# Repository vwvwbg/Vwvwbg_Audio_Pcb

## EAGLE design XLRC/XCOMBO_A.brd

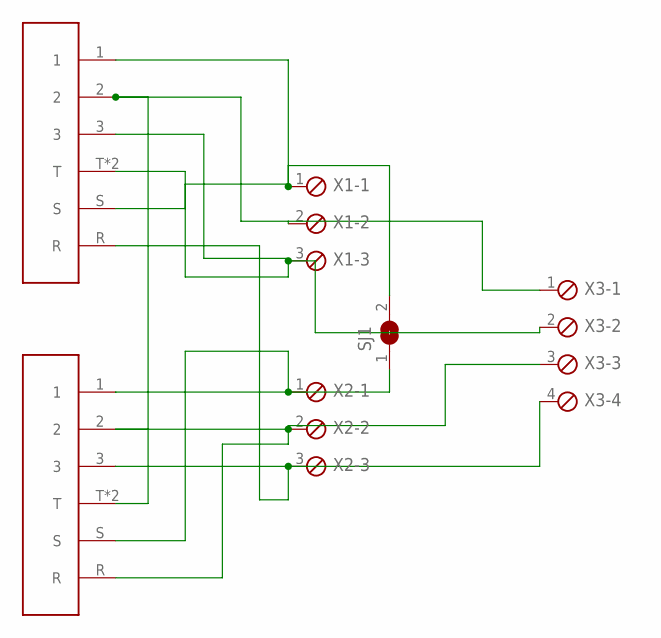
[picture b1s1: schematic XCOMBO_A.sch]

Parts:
SJ1: SJ
U$1, U$2: XLRCOMBOTYPEA; NCJ6FA-V-0
X1, X2: MPT3; 3POL254
X3: MPT4; 4POL254

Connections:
L+: U$1.T, U$1.T2 (T), U$2.2, X1.2, X3.1
L-: U$2.3, U$2.T, U$2.T2 (T), X1.3, X3.2
LG: SJ1.2, U$2.1, U$2.S, X1.1
R+: U$1.2, U$1.R, X2.2, X3.3
R-: U$1.3, U$2.R, X2.3, X3.4
RG: SJ1.1, U$1.1, U$1.S, X2.1

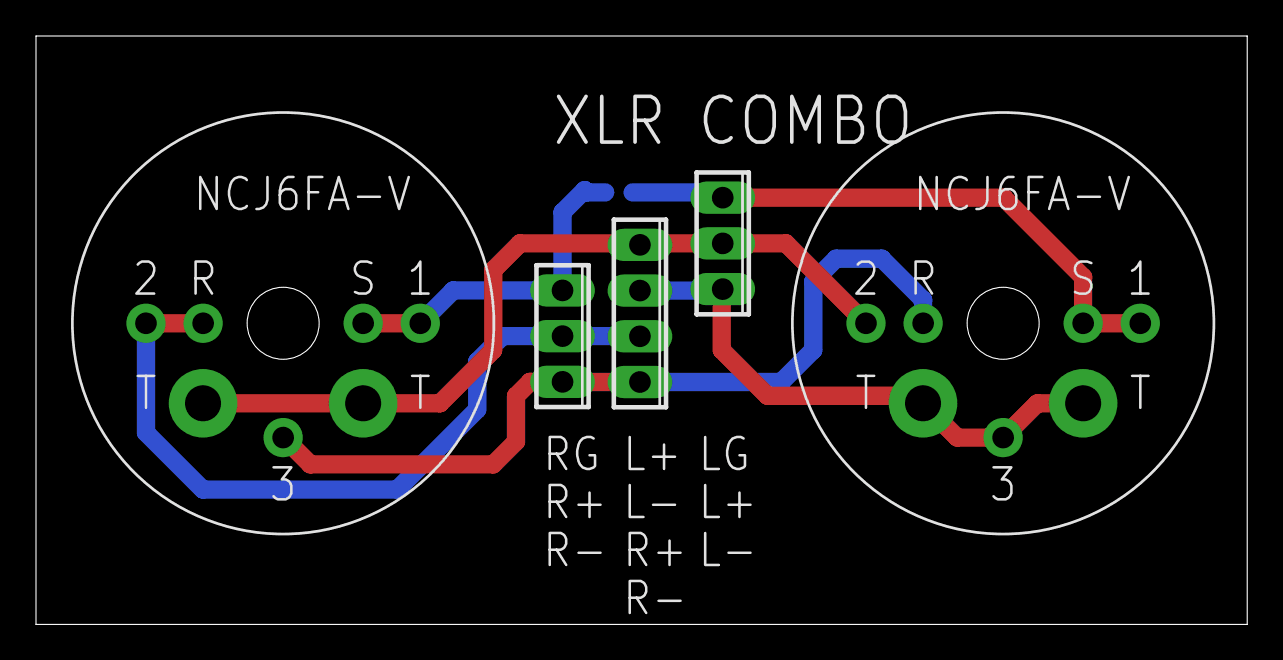
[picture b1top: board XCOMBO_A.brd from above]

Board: 2 copper layers, 67.3 x 32.7 mm, 6 parts (1 on the bottom side), 6 nets.

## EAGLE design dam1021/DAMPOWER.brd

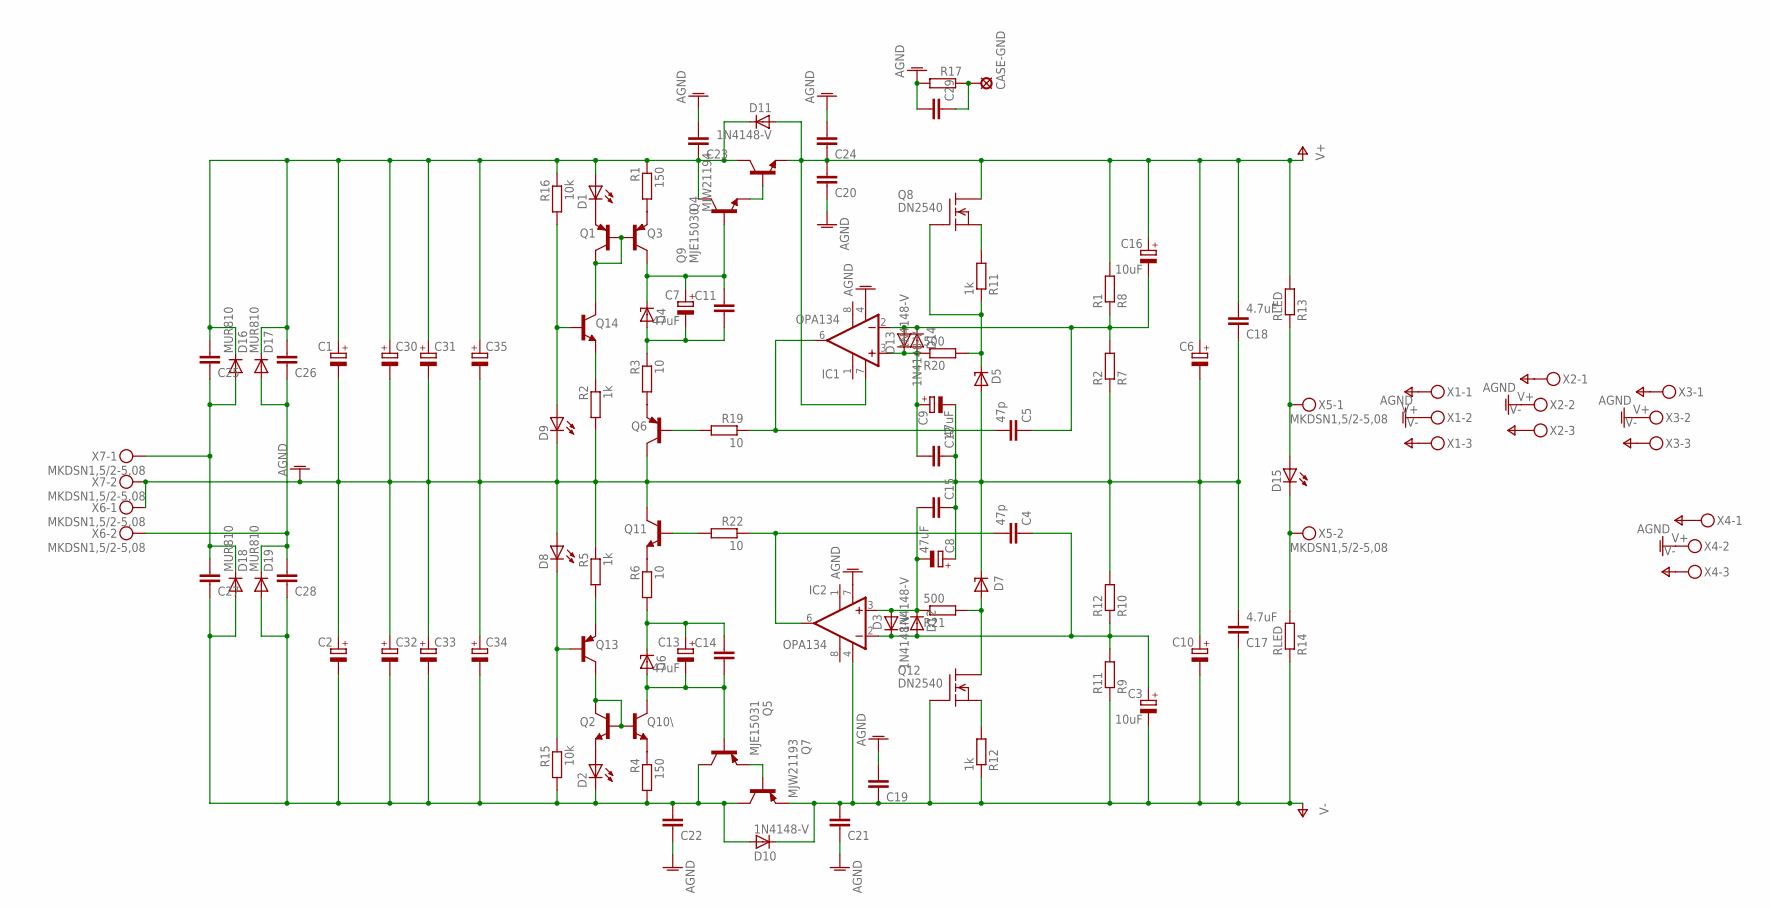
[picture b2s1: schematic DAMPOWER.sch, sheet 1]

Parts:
C1, C2: CPOL-EUE10-35; EB35D
C3, C16: 10uF; E5-8,5
C4, C5: 47p; C025_050-025X075
C6, C10, C30, C31, C32, C33, C34, C35: CPOL-EUE7.5-18; E7,5-18
C7, C8, C9, C13: 47uF; E5-8,5
C11, C12, C14, C15, C19, C20, C21, C24, C25, C26, C27, C28: C-EU050-035X075; C050-035X075
C17, C18: 4.7uF; C050-075X075
C22, C23: C-EU050-075X075; C050-075X075
C29: C-EU102_152-062X184; C102_152-062X184
CASE-GND: SE14
D1, D2, D8, D9, D15: LED5MM
D3, D10, D11, D12, D13, D14: 1N4148-V; 1N4148
D4, D6: 1N4728; DO41Z10
D5, D7: LT1021; DIL08
D16, D17, D18, D19: MUR810; TO220ACS
IC1, IC2: OPA134; DIL08
Q1, Q3, Q6, Q13: MPSA92-PNP-TO92-EBC; TO92-EBC
Q2, Q10\, Q11, Q14: MPSA42-NPN-TO92-EBC; TO92-EBC
Q4: MJW21194; TO-264
Q5: MJE15031; TO220KG
Q7: MJW21193; TO-264
Q8, Q12: DN2540; TO92-
Q9: MJE15030; TO220KG
R1, R4: 150; 0309/12
R2, R5, R11, R12: 1k; 0309/12
R3, R6, R19, R22: 10; 0309/12
R7: R2; 0309/12
R8: R1; 0309/12
R9: R11; 0309/12
R10: R12; 0309/12
R13, R14: RLED; 0309/12
R15, R16: 10k; 0309/12
R17: R-EU_0617/22; 0617/22
R20, R21: 500; 0309/12
X1, X2, X3, X4: MKDSN1,5/3-5,08
X5, X6, X7: MKDSN1,5/2-5,08

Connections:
AGND: C1.-, C2.+, C6.-, C8.+, C9.-, C10.+, C12.1, C15.1, C17.2, C18.1, C19.2, C20.1, C21.1, C22.1, C23.2, C24.2, C29.2, C29.3 (2), C30.-, C31.-, C32.+, C33.+, C34.+, C35.-, D5.4 (GND), D7.6 (OUT), D8.A, D9.K (C), IC1.4 (V-), IC2.7 (V+), Q6.C, Q11.C, R2.2, R5.1, R7.1, R10.2, R17.2, X1.2, X2.2, X3.2, X4.2, X6.1, X7.2
unnamed: Q1.B, Q1.C, Q3.B, Q14.C
unnamed: D1.K (C), Q1.E
unnamed: Q3.E, R1.2
unnamed: C1.+, C23.1, C25.2, C26.2, C30.+, C31.+, C35.+, D1.A, D11.C, D16.C, D17.C, Q4.C, Q9.2 (C), R1.1, R16.1
unnamed: C7.+, C11.1, D4.C, Q3.C, Q9.1 (B)
unnamed: C7.-, C11.2, D4.A, R3.1
unnamed: Q6.E, R3.2
unnamed: Q14.E, R2.1
unnamed: D9.A, Q14.B, R16.2
unnamed: C8.-, C15.2, D3.A, D12.C, IC2.3 (+IN), R21.1
unnamed: Q13.E, R5.2
unnamed: D8.K (C), Q13.B, R15.1
unnamed: Q11.E, R6.1
unnamed: C13.+, C14.1, D6.C, R6.2
unnamed: C13.-, C14.2, D6.A, Q5.1 (B), Q10\.C
unnamed: Q2.B, Q2.C, Q10\.B, Q13.C
unnamed: Q5.3 (E), Q7.B
unnamed: Q10\.E, R4.1
unnamed: D2.A, Q2.E
unnamed: Q4.B, Q9.3 (E)
unnamed: C2.-, C22.2, C27.1, C28.1, C32.-, C33.-, C34.-, D2.K (C), D10.A, D18.A, D19.A, Q5.2 (C), Q7.C, R4.2, R15.2
unnamed: C25.1, C27.2, D16.A, D18.C, X7.1
unnamed: C5.2, C5.3 (2), IC1.6 (OUT), R19.1
unnamed: C4.2, C4.3 (2), IC2.6 (OUT), R22.1
unnamed: Q11.B, R22.2
unnamed: Q6.B, R19.2
unnamed: C5.1, C16.-, D13.A, D14.C, IC1.2 (-IN), R7.2, R8.1
unnamed: Q12.3 (S), R12.2
unnamed: D5.6 (OUT), Q8.2 (G), R11.1, R20.2
unnamed: C9.+, C12.2, D13.C, D14.A, IC1.3 (+IN), R20.1
unnamed: D15.K (C), R14.2, X5.2
unnamed: D7.4 (GND), Q12.1 (D), R21.2
unnamed: C3.+, C4.1, D3.C, D12.A, IC2.2 (-IN), R9.2, R10.1
unnamed: Q8.3 (S), R11.2
unnamed: D15.A, R13.1, X5.1
unnamed: C26.1, C28.2, D17.A, D19.C, X6.2
unnamed: C29.1, CASE-GND.MP, R17.1
V+: C6.+, C16.+, C18.2, C20.2, C24.1, D11.A, IC1.7 (V+), Q4.E, Q8.1 (D), R8.2, R13.2, X1.1, X2.1, X3.1, X4.1
V-: C3.-, C10.-, C17.1, C19.1, C21.2, D10.C, IC2.4 (V-), Q7.E, Q12.2 (G), R9.1, R12.1, R14.1, X1.3, X2.3, X3.3, X4.3

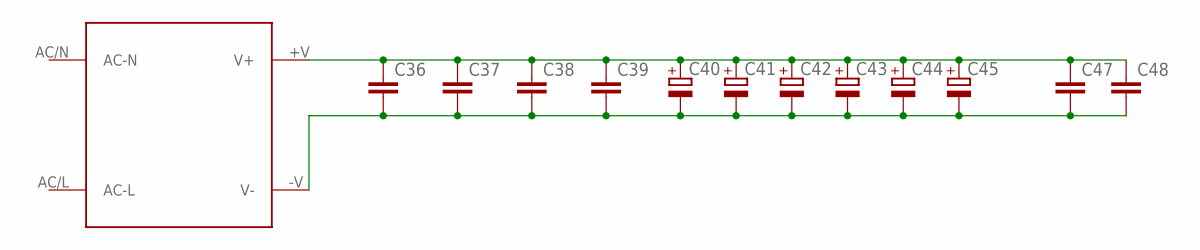
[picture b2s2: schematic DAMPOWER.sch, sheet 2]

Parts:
C36, C37, C38, C39, C47, C48: C-EU050-030X075; C050-030X075
C40, C41, C42, C43, C44, C45: CPOL-EUE3.5-8; E3,5-8
U$1: IRM-15-5; IRM-15

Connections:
unnamed: C36.1, C37.1, C38.1, C39.1, C40.+, C41.+, C42.+, C43.+, C44.+, C45.+, C47.1, C48.1, U$1.+V (V+)
unnamed: C36.2, C37.2, C38.2, C39.2, C40.-, C41.-, C42.-, C43.-, C44.-, C45.-, C47.2, C48.2, U$1.-V (V-)

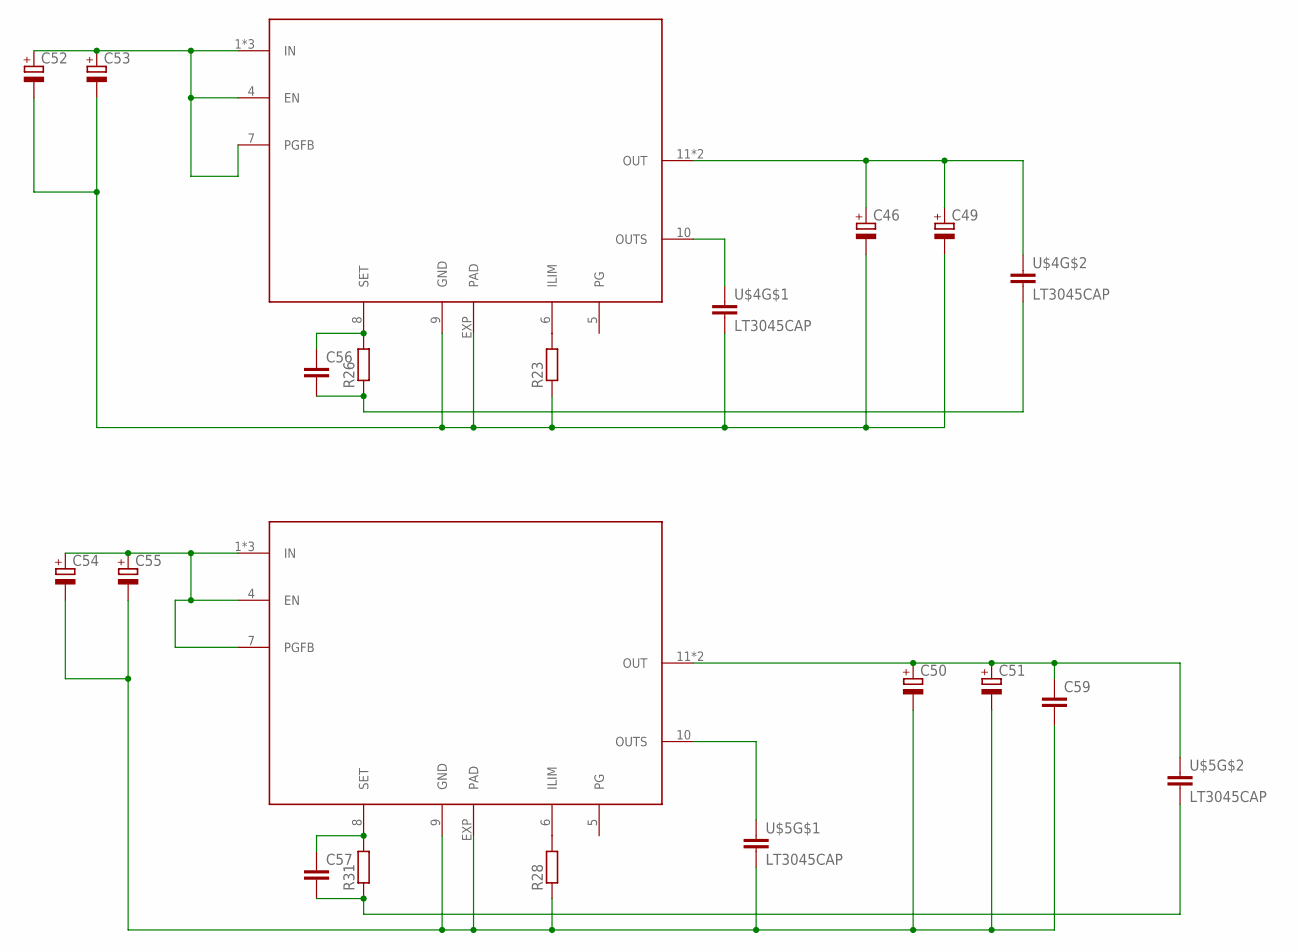
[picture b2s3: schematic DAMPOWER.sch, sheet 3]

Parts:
C46, C49, C50, C51: CPOL-EUE3.5-8; E3,5-8
C52, C53, C54, C55: CPOL-EUE5-10.5; E5-10,5
C56, C57, C59: C-EUC1210; C1210
R23, R26, R28, R31: R-EU_MELF0204R; MINI_MELF-0204R
U$2, U$3: LT3045; MSOP12
U$4, U$5: LT3045CAP

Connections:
unnamed: C52.+, C53.+, U$2.1 (IN), U$2.2 (IN), U$2.3 (IN), U$2.4 (EN), U$2.7 (PGFB)
unnamed: R23.2, U$2.6 (ILIM)
unnamed: C56.1, R26.2, U$2.8 (SET)
unnamed: R28.2, U$3.6 (ILIM)
unnamed: C57.1, R31.2, U$3.8 (SET)
unnamed: U$2.10 (OUTS), U$4.3 (1)
unnamed: C46.-, C49.-, C52.-, C53.-, R23.1, U$2.9 (GND), U$2.EXP (PAD), U$4.5 (2)
unnamed: C46.+, C49.+, U$2.11 (OUT), U$2.12 (OUT), U$4.4 (1)
unnamed: U$3.10 (OUTS), U$5.3 (1)
unnamed: C50.-, C51.-, C54.-, C55.-, C59.2, R28.1, U$3.9 (GND), U$3.EXP (PAD), U$5.5 (2)
unnamed: C56.2, R26.1, U$4.6 (2)
unnamed: C54.+, C55.+, U$3.1 (IN), U$3.2 (IN), U$3.3 (IN), U$3.4 (EN), U$3.7 (PGFB)
unnamed: C57.2, R31.1, U$5.6 (2)
unnamed: C50.+, C51.+, C59.1, U$3.11 (OUT), U$3.12 (OUT), U$5.4 (1)

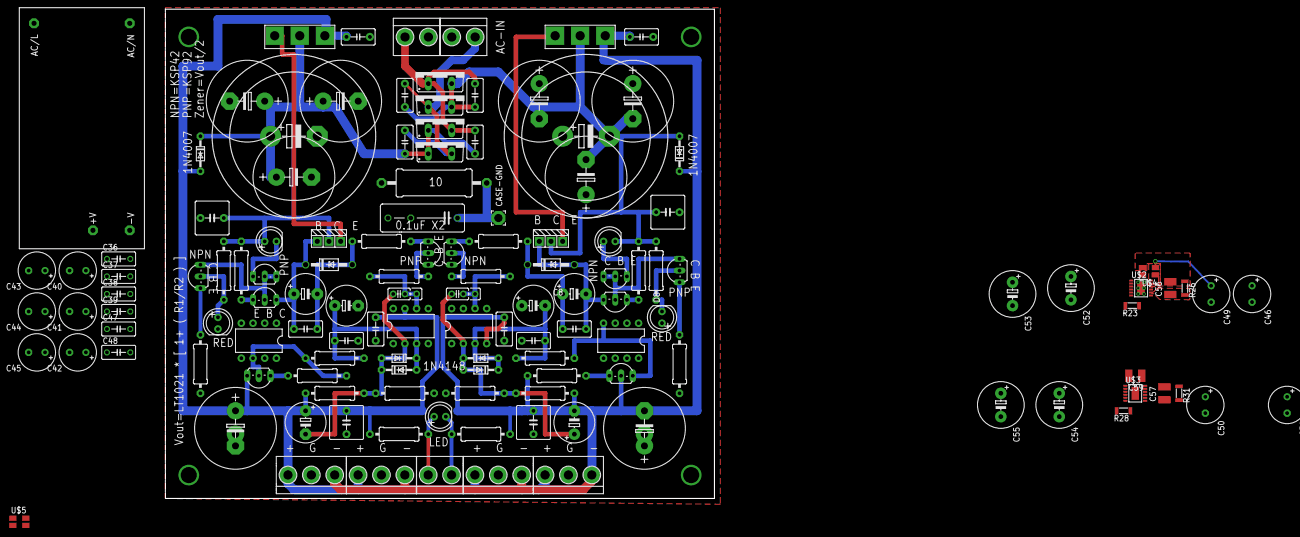
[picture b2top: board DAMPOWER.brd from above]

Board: 2 copper layers, 119.4 x 106.3 mm, 131 parts (0 on the bottom side), 56 nets.

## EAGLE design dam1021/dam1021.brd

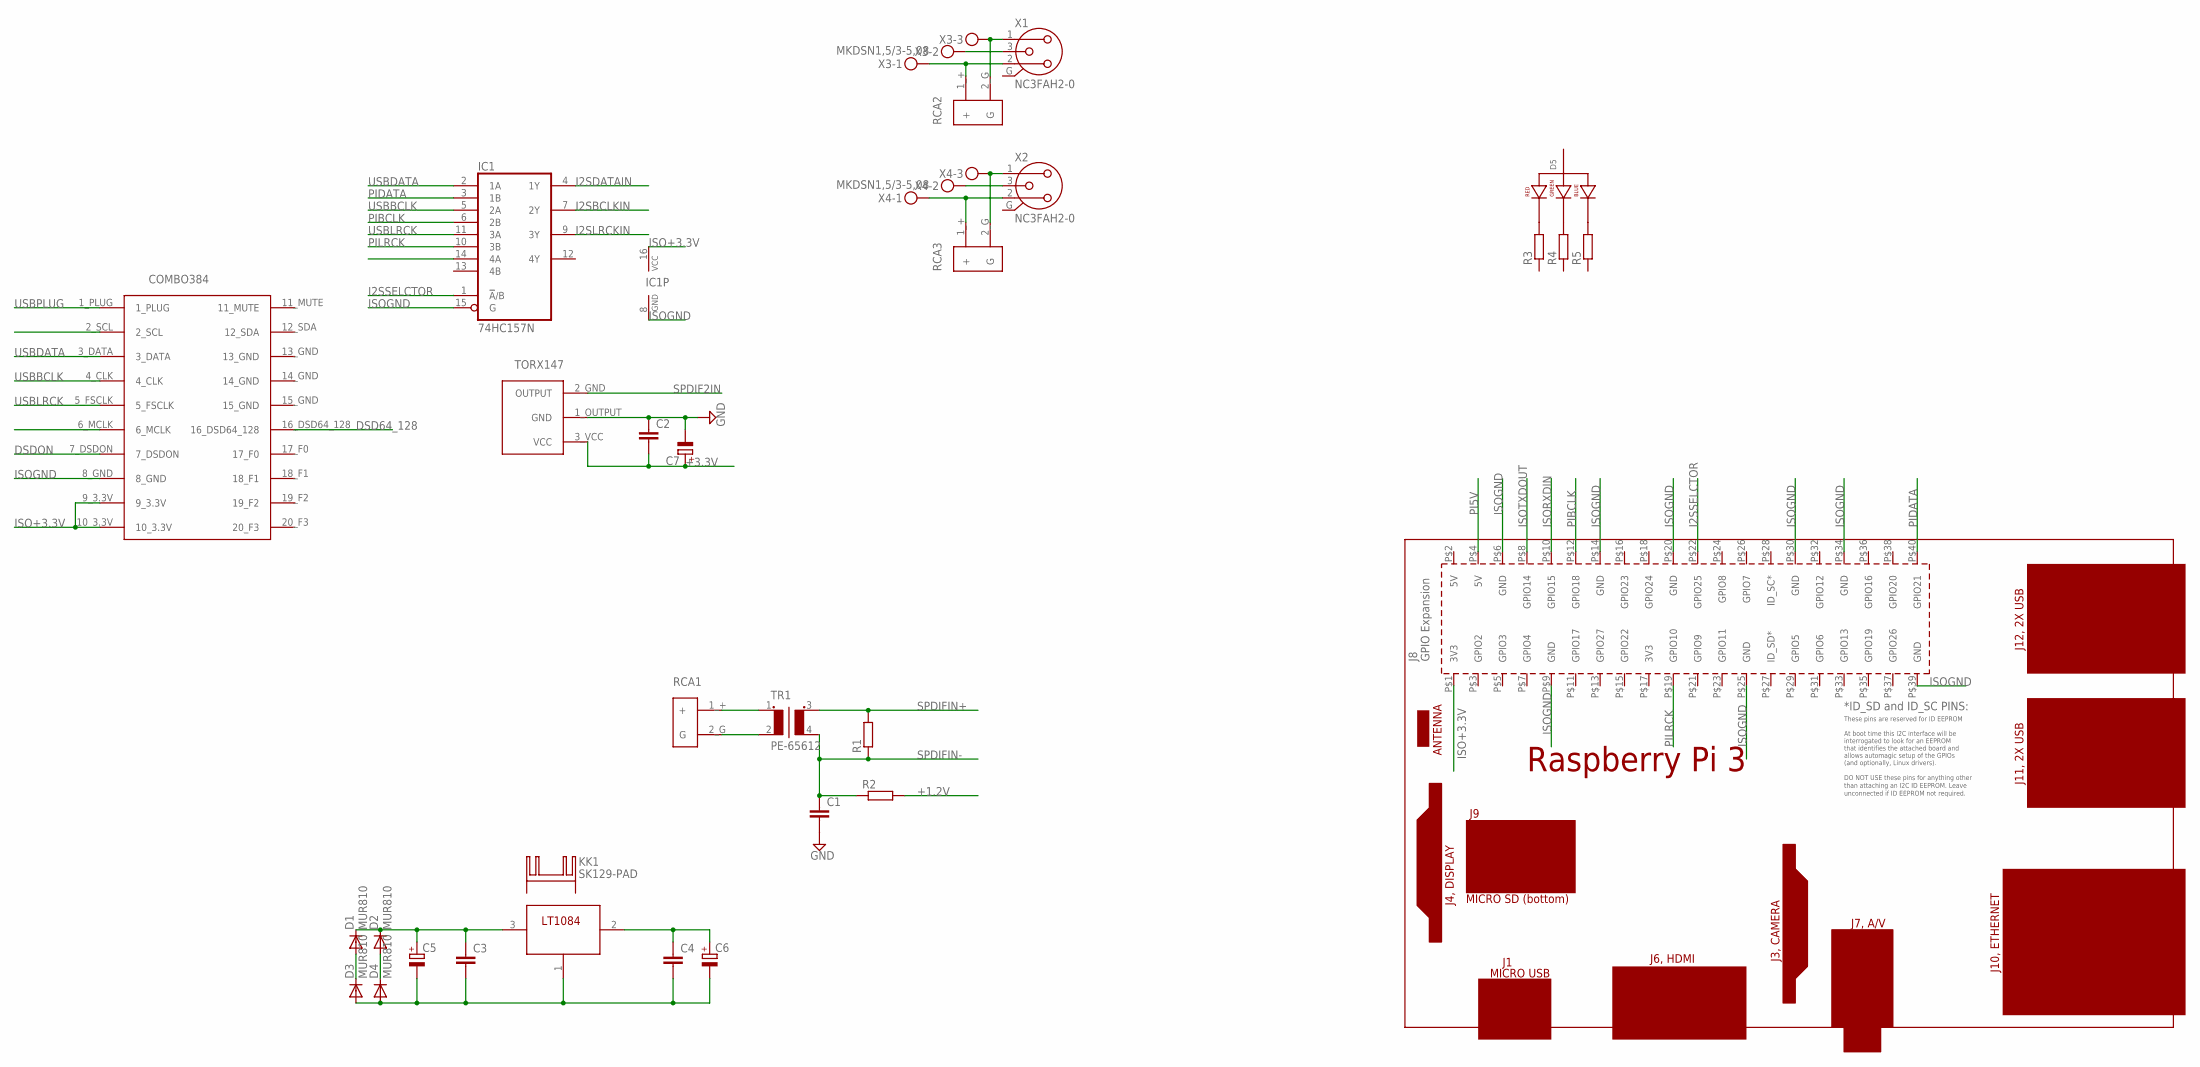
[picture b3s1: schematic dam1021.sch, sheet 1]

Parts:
C1, C2, C3, C4: C-EU050-035X075; C050-035X075
C5: CPOL-EUE7.5-16; E7,5-16
C6: CPOL-EUE5-10.5; E5-10,5
C7: CPOL-EUE2.5-7; E2,5-7
D1, D2, D3, D4: MUR810; TO220ACS
D5: LED-RGB-CA-THRUCLEAR; LED-RGB-THRU
IC1: 74HC157N; DIL16
KK1: SK129-PAD; SK129
PCB1: RPI3
R1, R2, R3, R4, R5: R-EU_0207/10; 0207/10
RCA1, RCA2, RCA3: RCA
TR1: PE-65612
U$2: TORX147
U$3: COMBO384
U$5: LT1084; TO-220
X1, X2: NC3FAH2-0
X3, X4: MKDSN1,5/3-5,08

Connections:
+1.2V: R2.2; also elsewhere on the board
+3.3V: C2.2, C7.+, U$2.3_VCC (VCC); also elsewhere on the board
AGND: RCA2.2_G (G), RCA3.2_G (G), X1.1, X2.1, X3.3, X4.3; also elsewhere on the board
DSD64_128: U$3.16_DSD64_128
DSDON: U$3.7_DSDON
GND: C1.2, C2.1, C7.-, U$2.1_OUTPUT (GND); also elsewhere on the board
I2SBCLKIN: IC1.7 (2Y); also elsewhere on the board
I2SDATAIN: IC1.4 (1Y); also elsewhere on the board
I2SLRCKIN: IC1.9 (3Y); also elsewhere on the board
I2SSELCTOR: IC1.1 (!A!/B), PCB1.P$22 (GPIO25)
ISO+3.3V: IC1.16 (VCC), PCB1.P$1 (3V3), U$3.9_3.3V, U$3.10_3.3V; also elsewhere on the board
ISOGND: C3.2, C4.2, C5.-, C6.-, D3.A, D4.A, IC1.8 (GND), IC1.15 (G), PCB1.P$6 (GND), PCB1.P$9 (GND), PCB1.P$14 (GND), PCB1.P$20 (GND), PCB1.P$25 (GND), PCB1.P$30 (GND), PCB1.P$34 (GND), PCB1.P$39 (GND), U$3.8_GND, U$5.1; also elsewhere on the board
ISORXDIN: PCB1.P$10 (GPIO15); also elsewhere on the board
ISOTXDOUT: PCB1.P$8 (GPIO14); also elsewhere on the board
unnamed: RCA1.1_+ (+), TR1.1
unnamed: RCA1.2_G (G), TR1.2 (3)
unnamed: D5.1 (RED_CATHODE), R3.2
unnamed: D5.3 (GREEN_CATHODE), R4.2
unnamed: C3.1, C5.+, D1.C, D2.C, U$5.3
unnamed: D1.A, D3.C
unnamed: D2.A, D4.C
unnamed: D5.4 (BLUE_CATHODE), R5.2
unnamed: X1.3, X3.2
unnamed: RCA2.1_+ (+), X1.2, X3.1
unnamed: X2.3, X4.2
unnamed: RCA3.1_+ (+), X2.2, X4.1
PI5V: C4.1, C6.+, PCB1.P$4 (5V), U$5.2
PIBCLK: IC1.6 (2B), PCB1.P$12 (GPIO18)
PIDATA: IC1.3 (1B), PCB1.P$40 (GPIO21)
PILRCK: IC1.10 (3B), PCB1.P$19 (GPIO10)
SPDIF2IN: U$2.2_GND (OUTPUT); also elsewhere on the board
SPDIFIN+: R1.2, TR1.3 (6); also elsewhere on the board
SPDIFIN-: C1.1, R1.1, R2.1, TR1.4; also elsewhere on the board
USBBCLK: IC1.5 (2A), U$3.4_CLK
USBDATA: IC1.2 (1A), U$3.3_DATA
USBLRCK: IC1.11 (3A), U$3.5_FSCLK
USBPLUG: U$3.1_PLUG

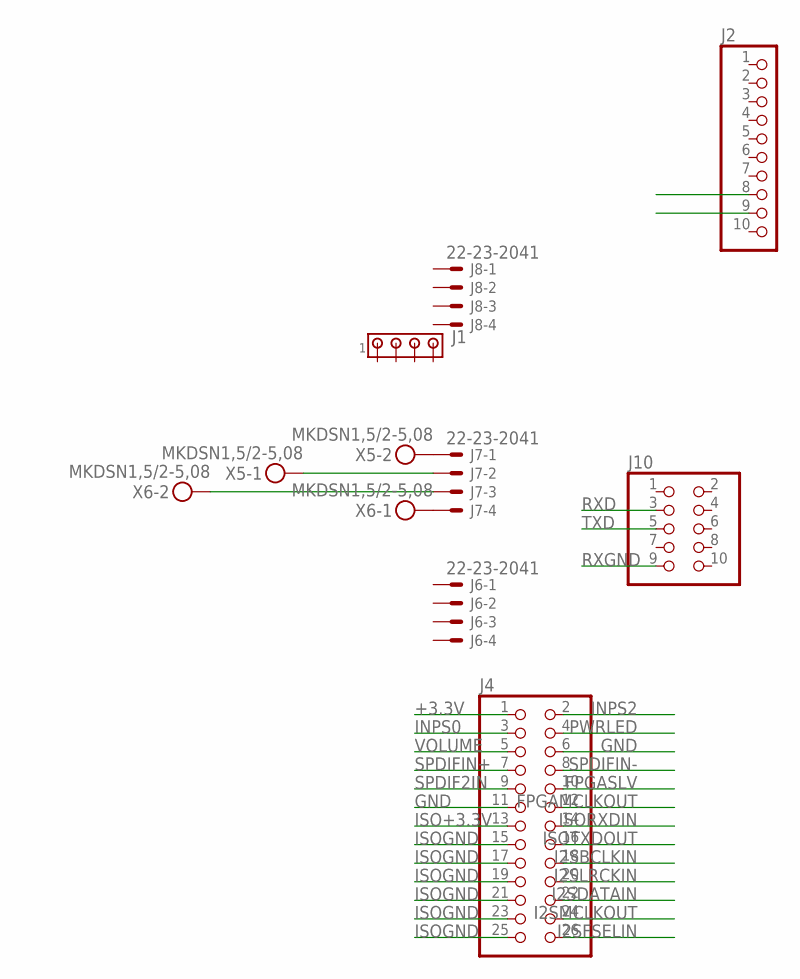
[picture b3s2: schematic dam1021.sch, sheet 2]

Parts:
J1: MTA04-156; 1X4MTA
J2: PINHD-1X10; 1X10
J4: PINHD-2X13; 2X13
J6, J7, J8: 22-23-2041
J10: PINHD-2X5; 2X05
X5, X6: MKDSN1,5/2-5,08

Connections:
+1.2V: J2.9; also elsewhere on the board
+3.3V: J2.8, J4.1; also elsewhere on the board
AGND: J7.2, J7.3, X5.1, X6.2; also elsewhere on the board
FPGAMCLKOUT: J4.12
FPGASLV: J4.10
GND: J4.6, J4.11; also elsewhere on the board
I2SBCLKIN: J4.18; also elsewhere on the board
I2SDATAIN: J4.22; also elsewhere on the board
I2SFSELIN: J4.26
I2SLRCKIN: J4.20; also elsewhere on the board
I2SMCLKOUT: J4.24
INPS0: J4.3
INPS2: J4.2
ISO+3.3V: J4.13; also elsewhere on the board
ISOGND: J4.15, J4.17, J4.19, J4.21, J4.23, J4.25; also elsewhere on the board
ISORXDIN: J4.14; also elsewhere on the board
ISOTXDOUT: J4.16; also elsewhere on the board
unnamed: J7.1, X5.2
unnamed: J7.4, X6.1
PWRLED: J4.4
RXD: J10.3
RXGND: J10.9
SPDIF2IN: J4.9; also elsewhere on the board
SPDIFIN+: J4.7; also elsewhere on the board
SPDIFIN-: J4.8; also elsewhere on the board
TXD: J10.5
VOLUME: J4.5

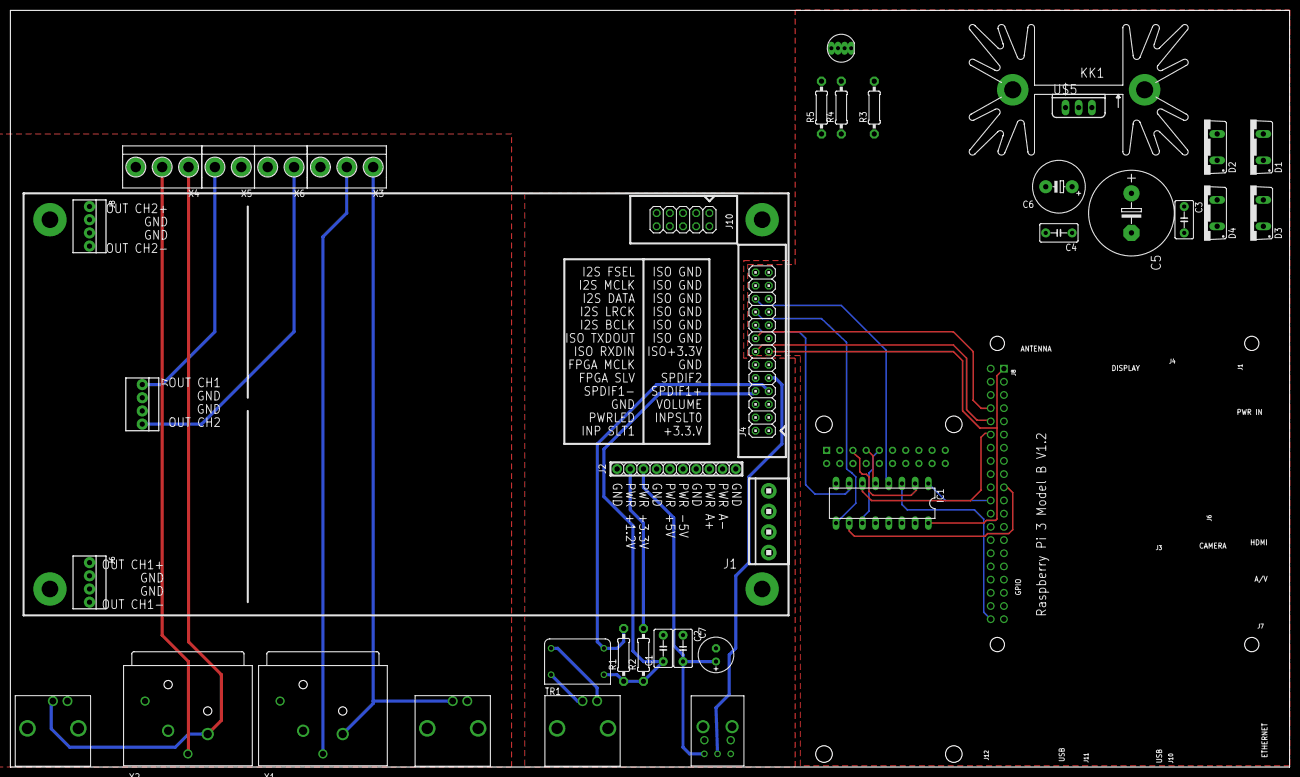
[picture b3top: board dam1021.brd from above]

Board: 2 copper layers, 246.4 x 145.7 mm, 40 parts (0 on the bottom side), 36 nets.

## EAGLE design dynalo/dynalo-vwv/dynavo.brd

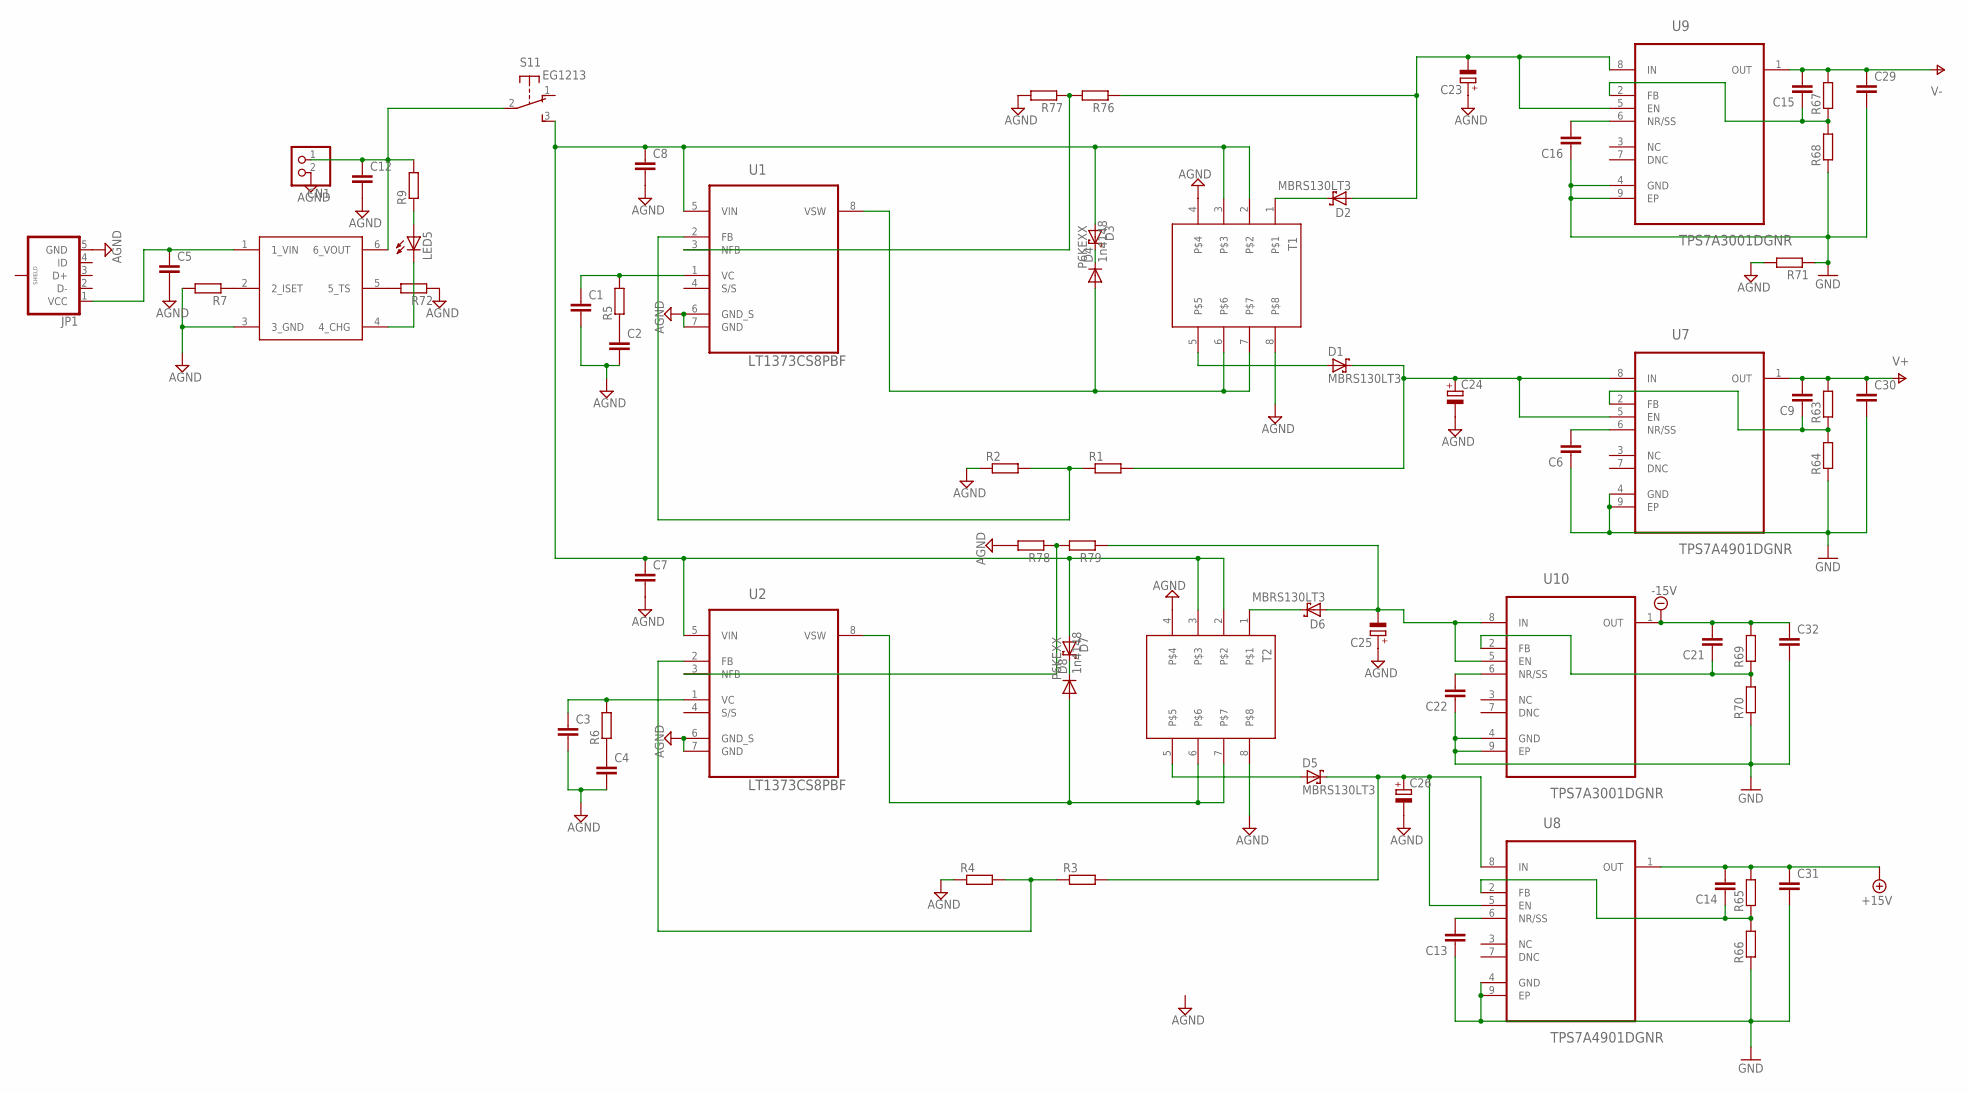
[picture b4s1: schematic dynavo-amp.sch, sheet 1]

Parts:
C1, C2, C3, C4, C5, C7, C8, C12: C-EUC1210; C1210
C6, C9, C13, C14, C15, C16, C21, C22, C29, C30, C31, C32: C-EUC1206; C1206
C23, C24, C25, C26: CPOL-EUD/7343-31W; D/7343-31W
CN1: JST_2PIN-THM; JST-PH-2-THM
D1, D2, D5, D6: MBRS130LT3; SMB
D3, D7: P6KEXX; SMBJ
D4, D8: 1n4148; SOD80C
JP1: USB_MICROB_PLUG-SMT; MICRO-B-SMT
LED5: LED3MM
R1, R2, R3, R4, R5, R6, R7, R9, R63, R64, R65, R66, R67, R68, R69, R70, R71, R72, R76, R77, R78, R79: R-EU_MELF0204W; MINI_MELF-0204W
S1: EG1213
T1, T2: LPE4841
U1, U2: LT1373CS8PBF; SOIC127P600X175-8N
U3: BQ21040; SOT-23-6
U7, U8: TPS7A4901DGNR; SOP65P490X110-9N
U9, U10: TPS7A3001DGNR; SOP65P490X110-9N

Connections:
+15V: C14.2, C31.1, R65.2, U8.1 (OUT); also elsewhere on the board
-15V: C21.2, C32.1, R69.2, U10.1 (OUT); also elsewhere on the board
AGND: C1.2, C2.2, C3.2, C4.2, C5.2, C7.2, C8.2, C12.2, C23.+, C24.-, C25.+, C26.-, CN1.2 (1), JP1.5 (GND), R2.1, R4.1, R7.2, R71.2, R72.1, R77.2, R78.2, T1.4, T1.8, T2.4, T2.8, U1.6 (GND_S), U1.7 (GND), U2.6 (GND_S), U2.7 (GND), U3.3 (3_GND)
GND: C6.1, C13.1, C16.1, C22.1, C29.2, C30.2, C31.2, C32.2, R64.1, R66.1, R68.1, R70.1, R71.1, U7.4 (GND), U7.9 (EP), U8.4 (GND), U8.9 (EP), U9.4 (GND), U9.9 (EP), U10.4 (GND), U10.9 (EP); also elsewhere on the board
unnamed: D3.C, D4.C
unnamed: C7.1, C8.1, D3.A, D7.A, S1.3 (S), T1.2, T1.3, T2.2, T2.3, U1.5 (VIN), U2.5 (VIN)
unnamed: D4.A, T1.6, T1.7, U1.8 (VSW)
unnamed: D2.C, T1.1
unnamed: D1.A, T1.5
unnamed: R1.1, R2.2, U1.2 (FB)
unnamed: R7.1, U3.2 (2_ISET)
unnamed: D7.C, D8.C
unnamed: D8.A, T2.6, T2.7, U2.8 (VSW)
unnamed: D6.C, T2.1
unnamed: D5.A, T2.5
unnamed: R3.1, R4.2, U2.2 (FB)
unnamed: C1.1, R5.2, U1.1 (VC)
unnamed: C3.1, R6.2, U2.1 (VC)
unnamed: C2.1, R5.1
unnamed: C4.1, R6.1
unnamed: LED5.A, R9.1
unnamed: C5.1, JP1.1 (VCC), U3.1 (1_VIN)
unnamed: C24.+, D1.C, R1.2, U7.5 (EN), U7.8 (IN)
unnamed: C23.-, D2.A, R76.1, U9.5 (EN), U9.8 (IN)
unnamed: C12.1, CN1.1 (2), R9.2, S1.2, U3.6 (6_VOUT)
unnamed: LED5.K (C), U3.4 (4_CHG)
unnamed: C26.+, D5.C, R3.2, U8.5 (EN), U8.8 (IN)
unnamed: C25.-, D6.A, R79.1, U10.5 (EN), U10.8 (IN)
unnamed: C9.1, R63.1, R64.2, U7.2 (FB)
unnamed: C14.1, R65.1, R66.2, U8.2 (FB)
unnamed: C15.1, R67.1, R68.2, U9.2 (FB)
unnamed: C16.2, U9.6 (NR/SS)
unnamed: C13.2, U8.6 (NR/SS)
unnamed: C21.1, R69.1, R70.2, U10.2 (FB)
unnamed: C6.2, U7.6 (NR/SS)
unnamed: C22.2, U10.6 (NR/SS)
unnamed: R72.2, U3.5 (5_TS)
unnamed: R76.2, R77.1, U1.3 (NFB)
unnamed: R78.1, R79.2, U2.3 (NFB)
V+: C9.2, C30.1, R63.2, U7.1 (OUT); also elsewhere on the board
V-: C15.2, C29.1, R67.2, U9.1 (OUT); also elsewhere on the board

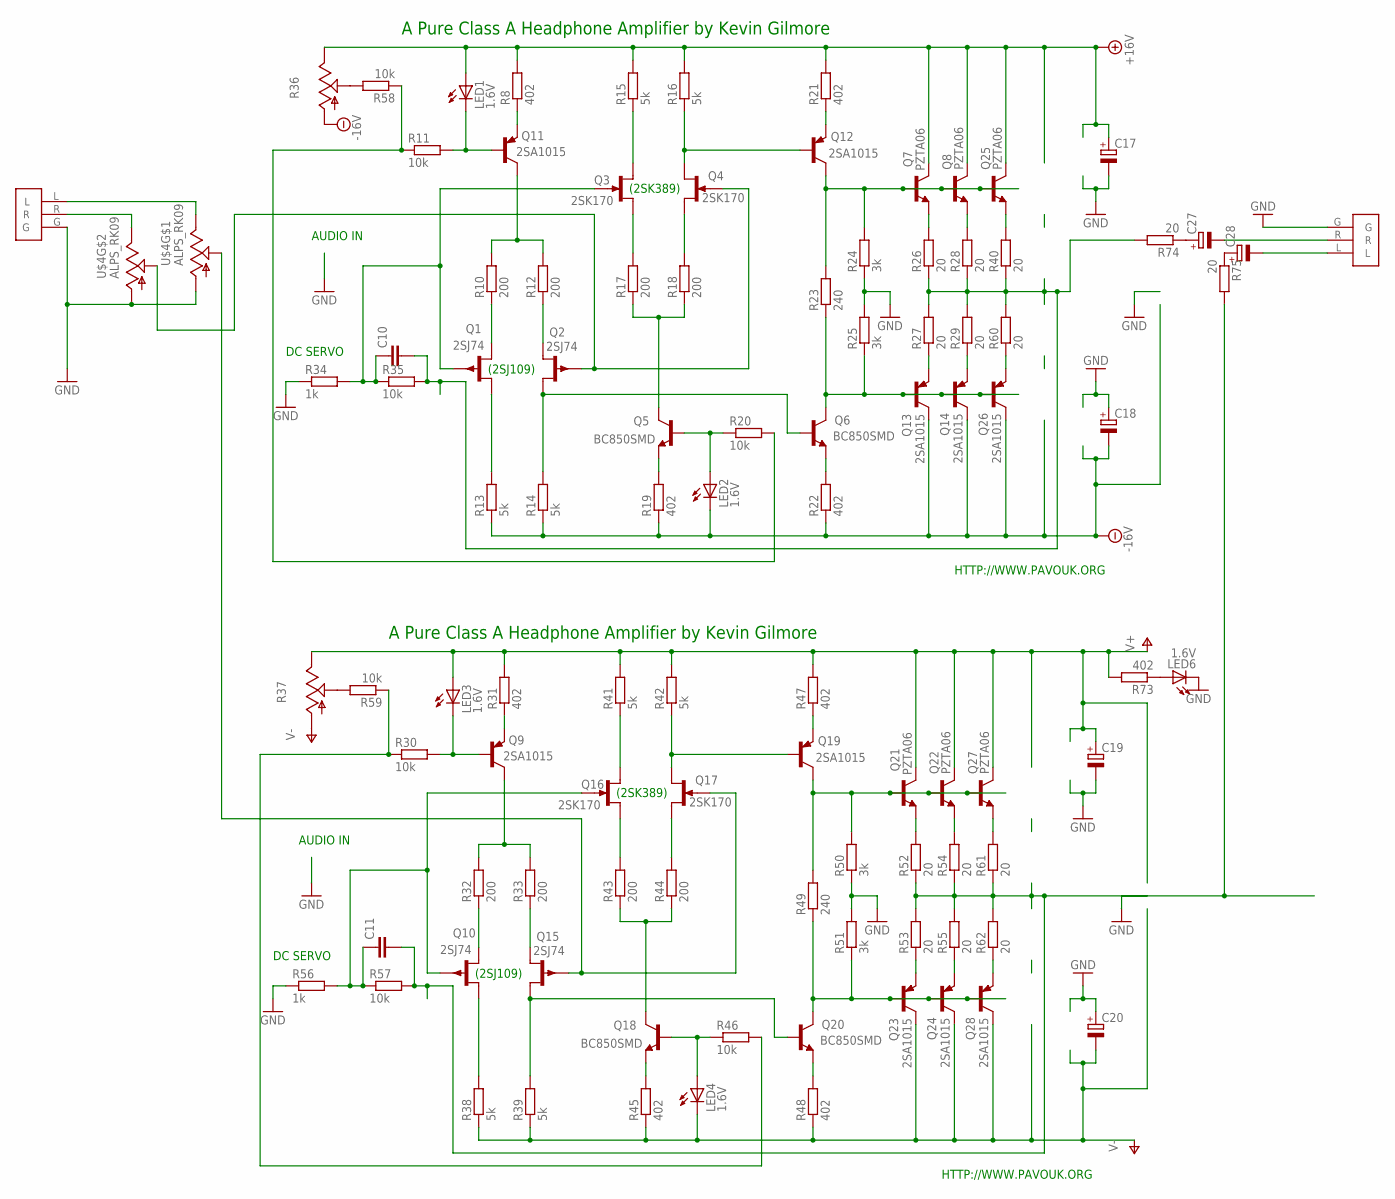
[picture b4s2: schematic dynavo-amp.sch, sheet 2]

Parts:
C10, C11: C-EUC1206; C1206
C17, C18, C19, C20, C27, C28: CPOL-EUD/7343-31W; D/7343-31W
LED1, LED2, LED3, LED4, LED6: 1.6V; CHIPLED_1206
Q1, Q2, Q10, Q15: 2SJ74; SOT23
Q3, Q4, Q16, Q17: 2SK170; SOT23
Q5, Q6, Q18, Q20: BC850SMD; SOT23-BEC
Q7, Q8, Q21, Q22, Q25, Q27: PZTA06; SOT223R_INFINEON
Q9, Q11, Q12, Q19: 2SA1015; SOT23-BEC
Q13, Q14, Q23, Q24, Q26, Q28: 2SA1015; SOT223R_INFINEON
R8, R19, R21, R22, R31, R45, R47, R48, R73: 402; MINI_MELF-0204W
R10, R12, R17, R18, R32, R33, R43, R44: 200; MINI_MELF-0204W
R11, R20, R30, R35, R46, R57, R58, R59: 10k; MINI_MELF-0204W
R13, R14, R15, R16, R38, R39, R41, R42: 5k; MINI_MELF-0204W
R23, R49: 240; MINI_MELF-0204W
R24, R25, R50, R51: 3k; MINI_MELF-0204W
R26, R27, R28, R29, R40, R52, R53, R54, R55, R60, R61, R62, R74, R75: 20; MINI_MELF-0204W
R34, R56: 1k; MINI_MELF-0204W
R36, R37: TRIM_US-3223G; 3223G
U$2, U$3: HPJACK; FOXCON-PHONEJACK
U$4: ALPS_RK09; RK09

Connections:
+15V: C17.+, LED1.A, Q7.2 (C), Q7.4 (C), Q8.2 (C), Q8.4 (C), Q25.2 (C), Q25.4 (C), R8.2, R15.2, R16.2, R21.2, R36.3 (E); also elsewhere on the board
-15V: C18.-, LED2.C, Q13.2 (C), Q13.4 (C), Q14.2 (C), Q14.4 (C), Q26.2 (C), Q26.4 (C), R13.1, R14.1, R19.1, R22.1, R36.1 (A); also elsewhere on the board
GND: C17.-, C18.+, C19.-, C20.+, LED6.C, R24.1, R25.2, R34.1, R50.1, R51.2, R56.1, U$2.G, U$3.G, U$4.G1 (1), U$4.G2 (1); also elsewhere on the board
unnamed: C10.2, R26.1, R27.2, R28.1, R29.2, R35.2, R40.1, R60.2, R74.2
unnamed: Q7.3 (E), R26.2
unnamed: Q8.3 (E), R28.2
unnamed: Q25.3 (E), R40.2
unnamed: Q13.3 (E), R27.1
unnamed: Q14.3 (E), R29.1
unnamed: Q26.3 (E), R60.1
unnamed: Q7.1 (B), Q8.1 (B), Q12.C, Q25.1 (B), R23.2, R24.2
unnamed: Q6.C, Q13.1 (B), Q14.1 (B), Q26.1 (B), R23.1, R25.1
unnamed: Q12.E, R21.1
unnamed: Q6.E, R22.2
unnamed: Q5.E, R19.2
unnamed: LED2.A, Q5.B, R20.1
unnamed: Q5.C, R17.1, R18.1
unnamed: Q4.2 (S), Q12.B, R16.1
unnamed: Q2.1 (D), Q6.B, R14.2
unnamed: Q11.C, R10.2, R12.2
unnamed: Q11.E, R8.1
unnamed: LED1.C, Q11.B, R11.2
unnamed: Q2.3 (G), Q4.3 (G), U$4.O2 (2)
unnamed: R36.2 (S), R58.2
unnamed: R37.2 (S), R59.2
unnamed: R11.1, R20.2, R58.1
unnamed: C10.1, Q1.3 (G), Q3.3 (G), R34.2, R35.1
unnamed: Q1.1 (D), R10.1
unnamed: Q2.2 (S), R12.1
unnamed: Q1.2 (S), R13.2
unnamed: Q3.1 (D), R15.1
unnamed: Q3.2 (S), R17.2
unnamed: Q4.1 (D), R18.2
unnamed: C11.2, R52.1, R53.2, R54.1, R55.2, R57.2, R61.1, R62.2, R75.2
unnamed: Q21.3 (E), R52.2
unnamed: Q22.3 (E), R54.2
unnamed: Q27.3 (E), R61.2
unnamed: Q23.3 (E), R53.1
unnamed: Q24.3 (E), R55.1
unnamed: Q28.3 (E), R62.1
unnamed: Q19.C, Q21.1 (B), Q22.1 (B), Q27.1 (B), R49.2, R50.2
unnamed: Q20.C, Q23.1 (B), Q24.1 (B), Q28.1 (B), R49.1, R51.1
unnamed: Q19.E, R47.1
unnamed: Q20.E, R48.2
unnamed: Q18.E, R45.2
unnamed: LED4.A, Q18.B, R46.1
unnamed: Q18.C, R43.1, R44.1
unnamed: Q17.2 (S), Q19.B, R42.1
unnamed: Q15.1 (D), Q20.B, R39.2
unnamed: Q9.C, R32.2, R33.2
unnamed: Q9.E, R31.1
unnamed: LED3.C, Q9.B, R30.2
unnamed: Q15.3 (G), Q17.3 (G), U$4.O1 (2)
unnamed: R30.1, R46.2, R59.1
unnamed: C11.1, Q10.3 (G), Q16.3 (G), R56.2, R57.1
unnamed: Q10.1 (D), R32.1
unnamed: Q15.2 (S), R33.1
unnamed: Q10.2 (S), R38.2
unnamed: Q16.1 (D), R41.1
unnamed: Q16.2 (S), R43.2
unnamed: Q17.1 (D), R44.2
unnamed: U$3.R, U$4.I2 (3)
unnamed: U$3.L, U$4.I1 (3)
unnamed: C27.-, U$2.R
unnamed: C28.-, U$2.L
unnamed: LED6.A, R73.1
unnamed: C27.+, R74.1
unnamed: C28.+, R75.1
V+: C19.+, LED3.A, Q21.2 (C), Q21.4 (C), Q22.2 (C), Q22.4 (C), Q27.2 (C), Q27.4 (C), R31.2, R37.3 (E), R41.2, R42.2, R47.2, R73.2; also elsewhere on the board
V-: C20.-, LED4.C, Q23.2 (C), Q23.4 (C), Q24.2 (C), Q24.4 (C), Q28.2 (C), Q28.4 (C), R37.1 (A), R38.1, R39.1, R45.1, R48.1; also elsewhere on the board

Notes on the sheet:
A Pure Class A Headphone Amplifier by Kevin Gilmore
HTTP://WWW.PAVOUK.ORG
DC SERVO
AUDIO IN
(2SK389)
(2SJ109)

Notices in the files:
parts and their libraries:
SparkFun-LED: Licensing: Creative Commons ShareAlike 4.0 International - https://creativecommons.org/licenses/by-sa/4.0
